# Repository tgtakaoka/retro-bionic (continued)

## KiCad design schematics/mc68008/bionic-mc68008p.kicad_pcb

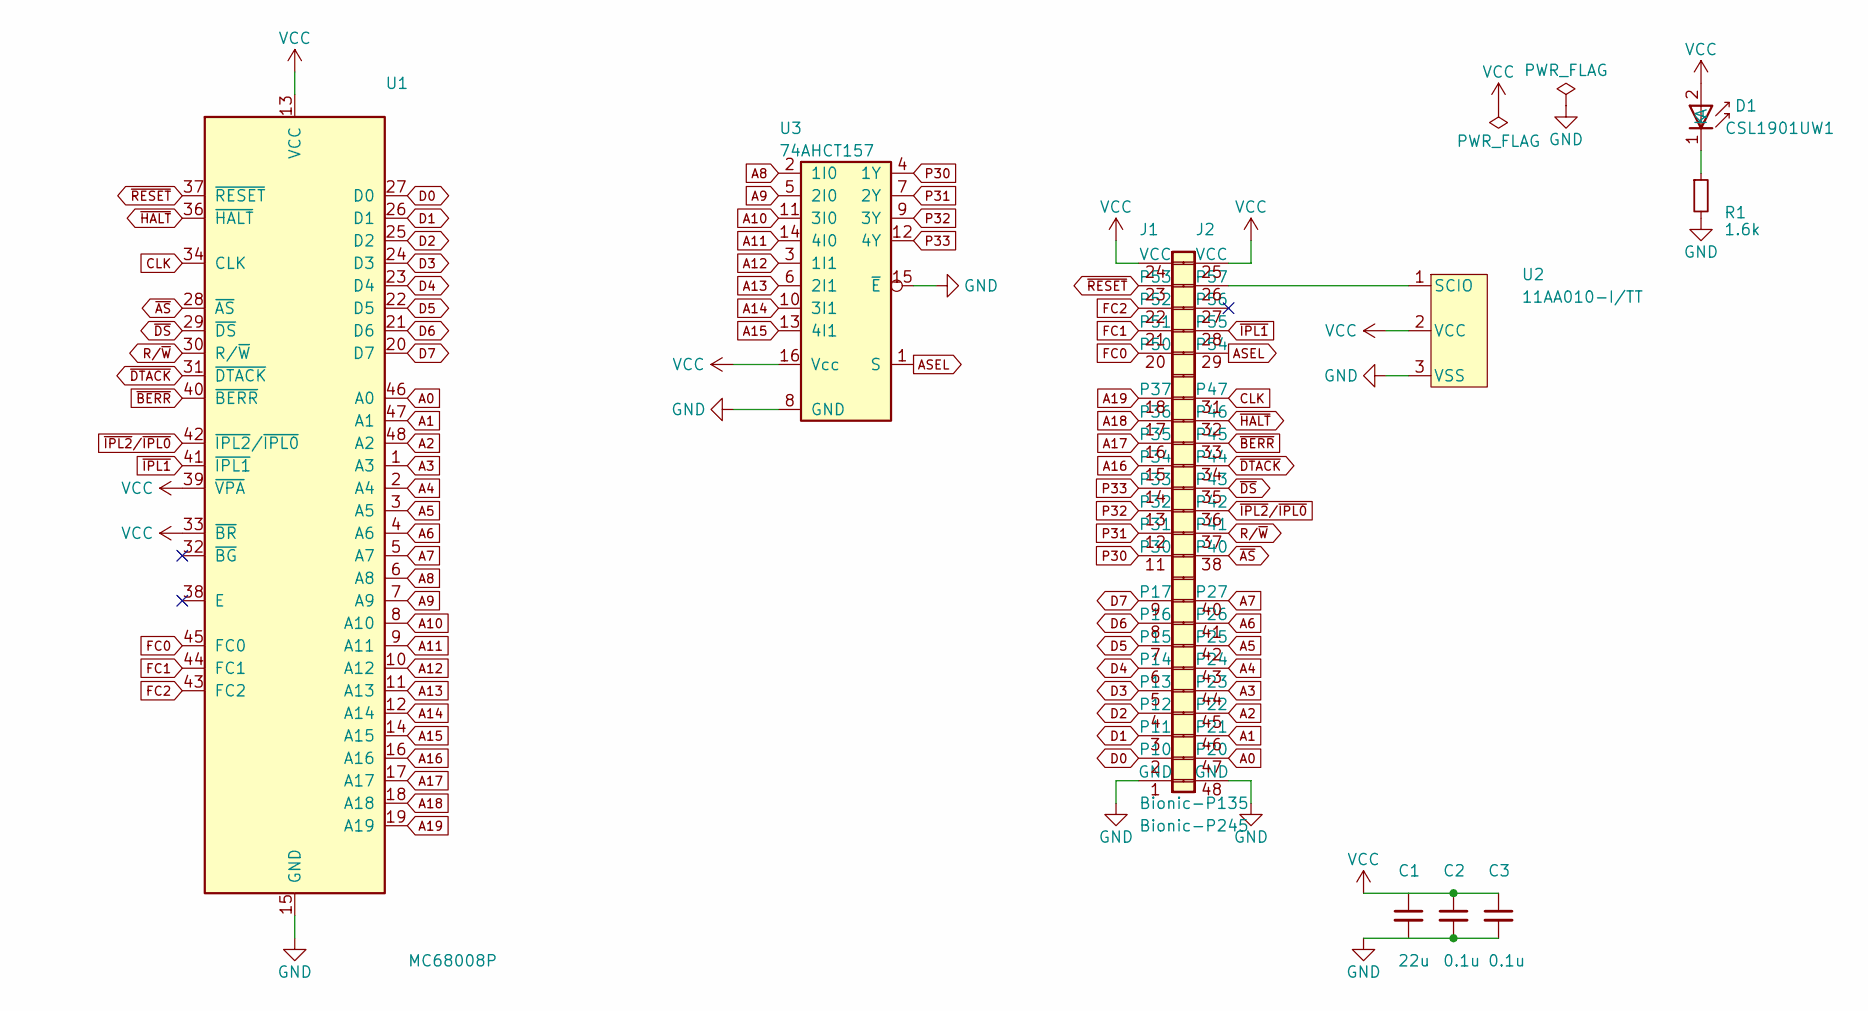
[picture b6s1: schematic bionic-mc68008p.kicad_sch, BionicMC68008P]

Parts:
C1: 22u; C_0603_1608Metric_Pad1.08x0.95mm_HandSolder
C2, C3: 0.1u; C_0603_1608Metric_Pad1.08x0.95mm_HandSolder
D1: CSL1901UW1; LED_CSL1901UW1_ROM-M
J1: Bionic-P135; Bionic-P135_THT
J2: Bionic-P245; Bionic-P245_THT
R1: 1.6k; R_0603_1608Metric_Pad0.98x0.95mm_HandSolder
U1: MC68008P; DIP-48_W15.24mm_Socket
U2: 11AA010-I/TT; SOT-23_MC_MCH-M
U3: 74AHCT157; PW16-M

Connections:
A0: J2.47 (P20), U1.46 (A0)
A1: J2.46 (P21), U1.47 (A1)
A2: J2.45 (P22), U1.48 (A2)
A3: J2.44 (P23), U1.1 (A3)
A4: J2.43 (P24), U1.2 (A4)
A5: J2.42 (P25), U1.3 (A5)
A6: J2.41 (P26), U1.4 (A6)
A7: J2.40 (P27), U1.5 (A7)
A8: U1.6 (A8), U3.2 (1I0)
A9: U1.7 (A9), U3.5 (2I0)
A10: U1.8 (A10), U3.11 (3I0)
A11: U1.9 (A11), U3.14 (4I0)
A12: U1.10 (A12), U3.3 (1I1)
A13: U1.11 (A13), U3.6 (2I1)
A14: U1.12 (A14), U3.10 (3I1)
A15: U1.14 (A15), U3.13 (4I1)
A16: J1.15 (P34), U1.16 (A16)
A17: J1.16 (P35), U1.17 (A17)
A18: J1.17 (P36), U1.18 (A18)
A19: J1.18 (P37), U1.19 (A19)
ASEL: J2.29 (P54), U3.1 (S)
CLK: J2.31 (P47), U1.34 (CLK)
D0: J1.2 (P10), U1.27 (D0)
D1: J1.3 (P11), U1.26 (D1)
D2: J1.4 (P12), U1.25 (D2)
D3: J1.5 (P13), U1.24 (D3)
D4: J1.6 (P14), U1.23 (D4)
D5: J1.7 (P15), U1.22 (D5)
D6: J1.8 (P16), U1.21 (D6)
D7: J1.9 (P17), U1.20 (D7)
FC0: J1.20 (P50), U1.45 (FC0)
FC1: J1.21 (P51), U1.44 (FC1)
FC2: J1.22 (P52), U1.43 (FC2)
GND: C1.2, C2.2, C3.2, J1.1 (GND), J2.48 (GND), R1.2, U1.15 (GND), U1.35 (GND), U2.3 (VSS), U3.8 (GND), U3.15 (~E)
unnamed: D1.1 (K), R1.1
unnamed: J2.26 (P57), U2.1 (SCIO)
P30: J1.11 (P30), U3.4 (1Y)
P31: J1.12 (P31), U3.7 (2Y)
P32: J1.13 (P32), U3.9 (3Y)
P33: J1.14 (P33), U3.12 (4Y)
R/~W: J2.37 (P41), U1.30 (R/~W)
VCC: C1.1, C2.1, C3.1, D1.2 (A), J1.24 (VCC), J2.25 (VCC), U1.13 (VCC), U1.33 (~BR), U1.39 (~VPA), U2.2 (VCC), U3.16 (Vcc)
~AS: J2.38 (P40), U1.28 (~AS)
~BERR: J2.33 (P45), U1.40 (~BERR)
~DS: J2.35 (P43), U1.29 (~DS)
~DTACK: J2.34 (P44), U1.31 (~DTACK)
~HALT: J2.32 (P46), U1.36 (~HALT)
~IPL1: J2.28 (P55), U1.41 (~IPL1)
~IPL2/~IPL0: J2.36 (P42), U1.42 (~IPL2/~IPL0)
~RESET: J1.23 (P53), U1.37 (~RESET)

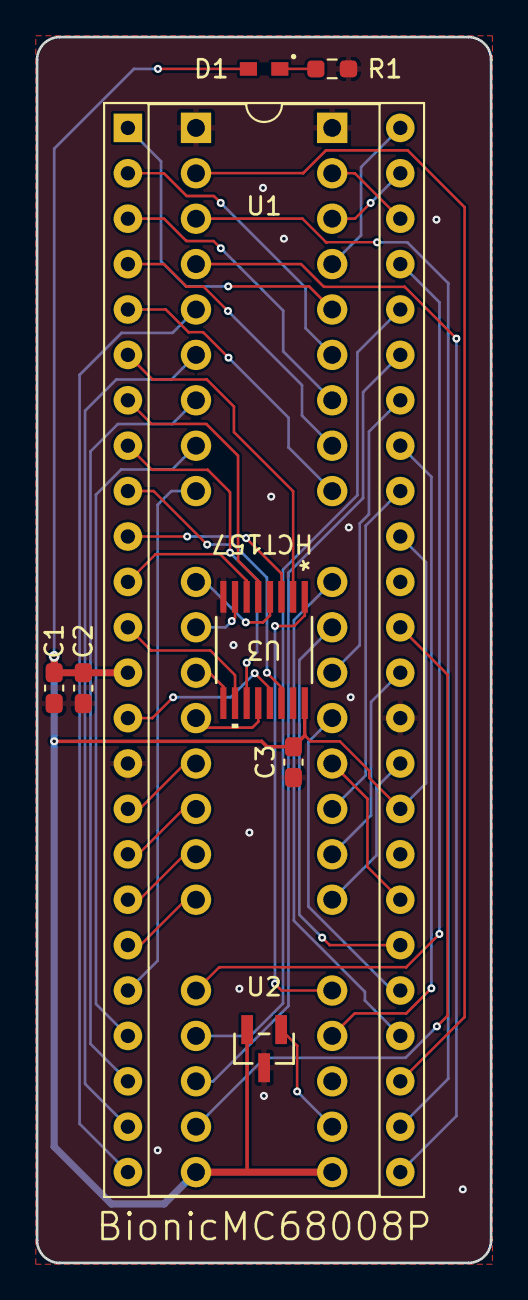
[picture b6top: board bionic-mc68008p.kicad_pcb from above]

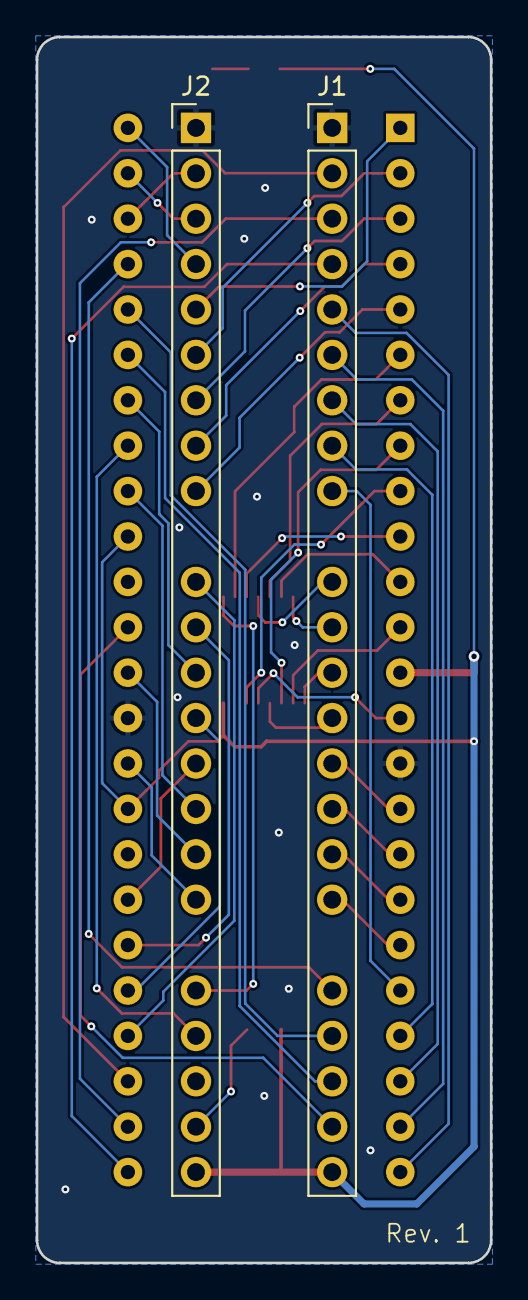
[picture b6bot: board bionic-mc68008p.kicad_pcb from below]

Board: 2 copper layers, 25.4 x 68.6 mm, 10 parts (2 on the bottom side), 50 nets.
